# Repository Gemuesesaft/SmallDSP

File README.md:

# SmallDSP
a small, modular and affordable Audio DSP Module

The goal of this Project is to create a line-up of small DSP modules, centred
around an Analog Devices ADAU1463/67.
This Chip is easy to program with Sigma Studio, a node based development 
environment and pretty powerful for its price.

Current status:
- Dual: Rev 1.1: Layout finished, functionality has to be validated.
- Maxi: Rev 1.0: Layout finished, ,prototype ordered, 
    functionality has to be validated.
- Multi: Rev 1.0: Schematic unfinished.
- Mini: Nothing done yet.
- Micro: Nothing done yet.
- Digi: Nothing done yet.

I've planed for 6 different modules:

- A compact one with two analogue input and output channels (SmallDSP Dual).
- A very small with only digital I2S IOs (SmallDSP Digi).
- A very small module with only one analogue input and output (SmallDSPMini).
- A similar than the Mini, but with and Microphone preamp (SmallDSP Micro). 
    Perhaps powered by phantom power.
- One with 16 analogue IOs (SmallDSP Multi).
- And one with 32 analogue IOs (SmallDSP Maxi).

There are three different versions of the used DSP Chip:
- The ADAU1463WBCPZ150. This is a slower version (max. 150MHz) with 48kWords 
    data memory and 16kWords program memory. Optimal for the smaller Boards
    like the Dual, Mini or Micro.
- The ADAU1463WBCPZ300. This is a faster version (max. 300MHz) with the same
    48kWords data memory and 16kWords program memory. Well suited for heavy
    processing or many channels, for example the Multi or Maxi.
- And the ADAU1467WBCPZ300. This is also a faster version (max. 300MHz) with
    more memory 80kWords data and 24kWords program memory. The expanded memory
    is useful if long delays on multiple channels are required.
All versions are pin-compatible, so one can use the version, best suited for 
the use case. 

The Dual, Digi, Mini and if phantom power isn't possible, the Micro, shall be
powered by a single output wall brick power supply. Both Multi and Maxi are 
using a +-5V power supply and feature a PE connection. They are therefore
designed for a metal enclosure such a 19" Rack enclosure. 

I try to maximize the components covered by JLCPCBs Basic Parts library, so
the boards can be manufactured cheaply and easily. Unfortunately this doesn't
cover all components, so there is still some hand soldering necessary. 

I tried to avoid the use of a Microcontroller, because the DSP can do pretty
much everything on itself. Although the DSP can act as a I2C or SPI master, I 
used ADCs and DAC that are configured directly by setting specific pins,
because the usage of the I2C/SPI master feature an ADAU DSPs is, at least
to my knowledge, not very user-friendly. Please correct me if I'm wrong there 
I would very much like to know an easy way to use this feature.
The Maxi is an exception in that, as it has a STM32 MCU on board. That is 
because the used Codecs are only controllable over I2C/SPI and are way cheaper
than pin-controllable alternatives.

A detailed documentation is planned, but the current focus lies on finishing
the PCBs and the testing of those. Detailed performance measurements will
be published here as well, as soon as they are made.

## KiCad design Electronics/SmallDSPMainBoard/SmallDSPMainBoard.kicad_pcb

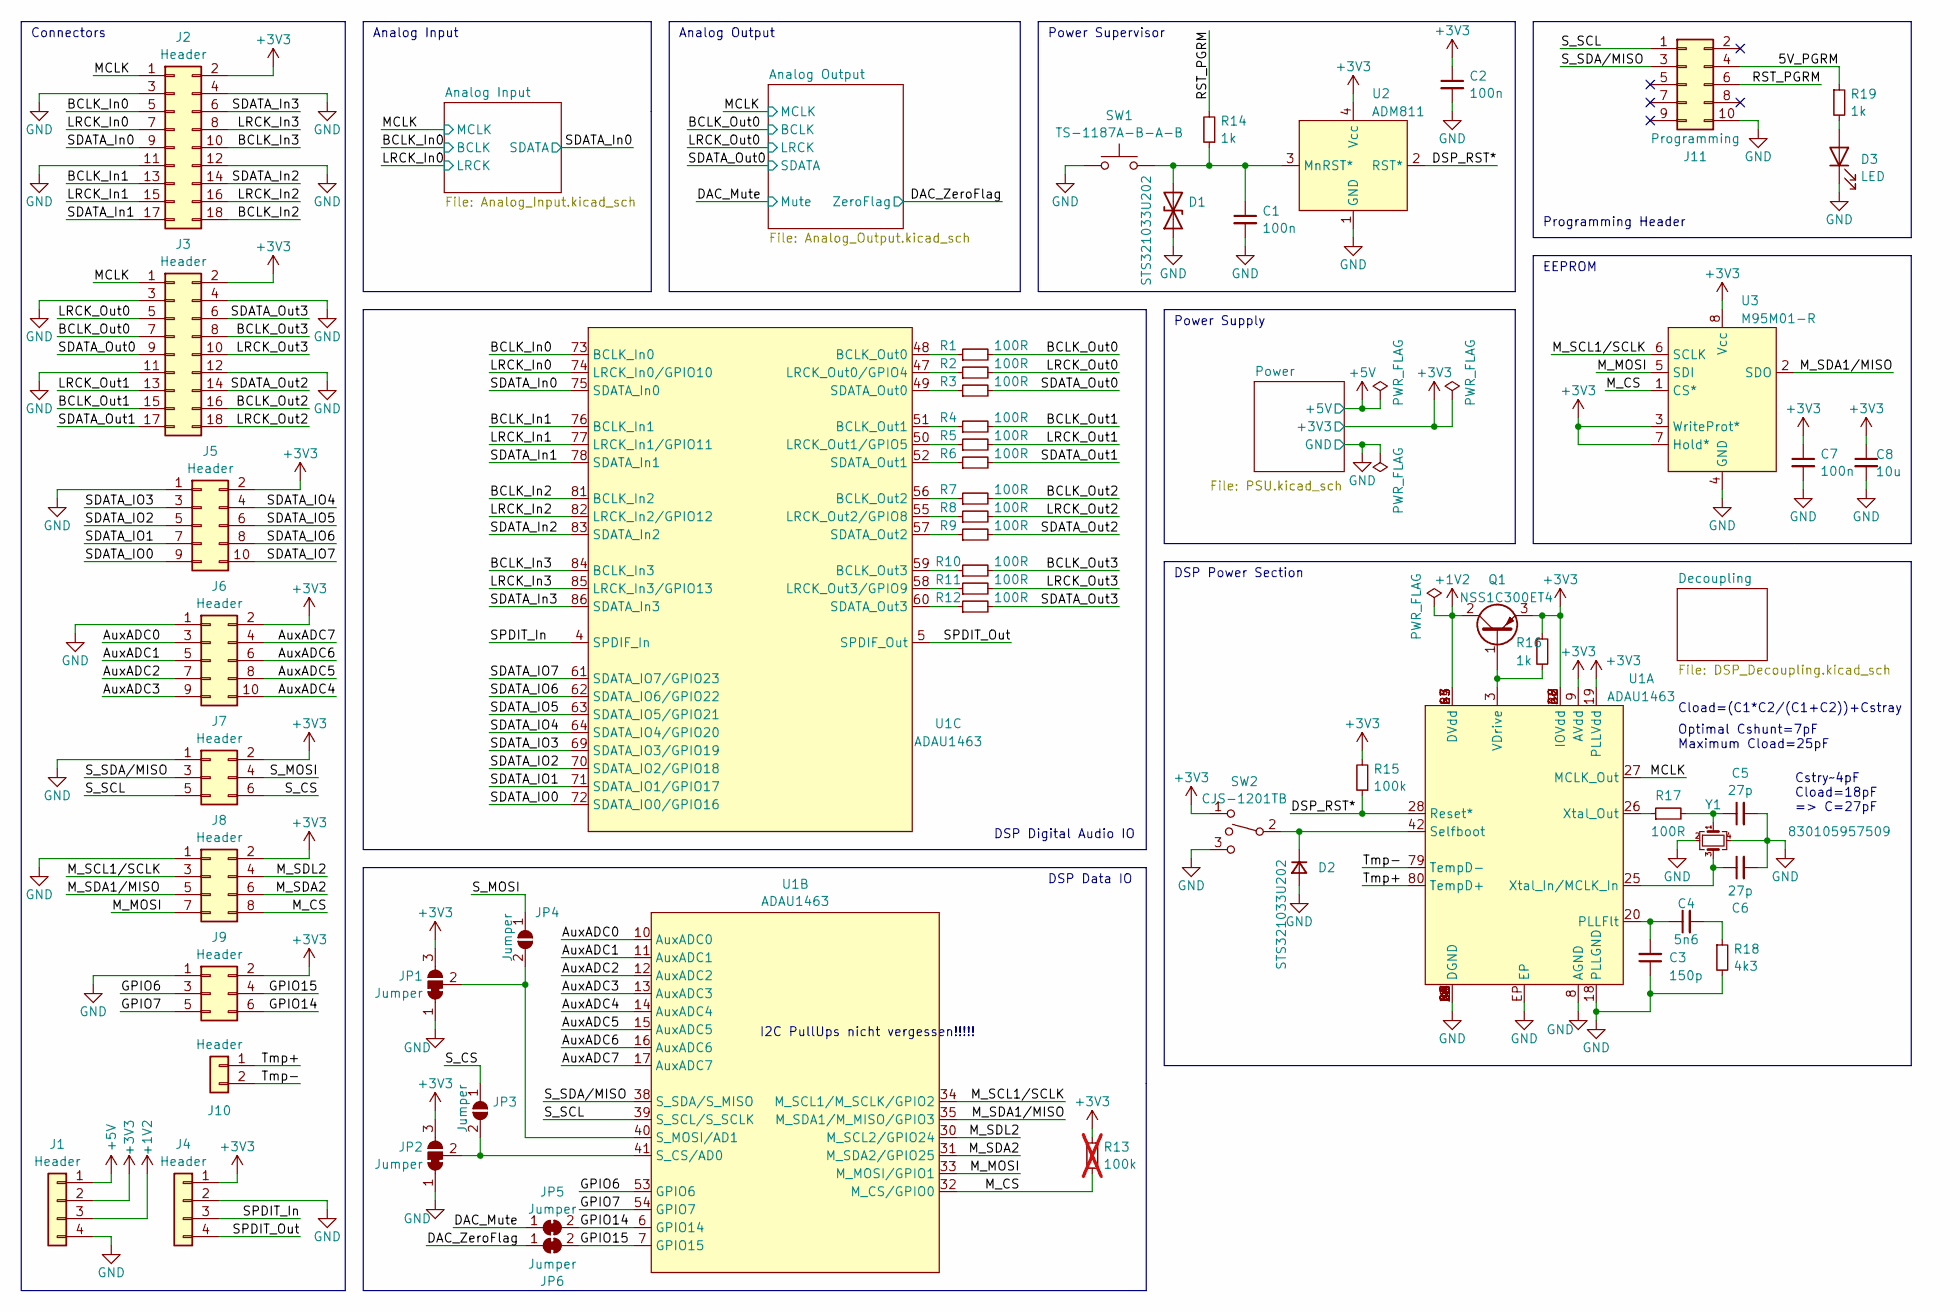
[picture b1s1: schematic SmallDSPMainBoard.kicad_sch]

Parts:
C1, C2, C7: 100n; C_0402_1005Metric; Rated Voltage 16V; Part Number CL05B104KO5NNNC; JLC Part Number C1525
C3: 150p; C_0402_1005Metric; Rated Voltage 50V; Part Number 0402B151K500NT; JLC Part Number C1527
C4: 5n6; C_0603_1608Metric_Pad1.08x0.95mm_HandSolder; Rated Voltage 50V; Part Number GRM1885C1H562JA01D
C5, C6: 27p; C_0402_1005Metric; Rated Voltage 50V; Part Number 0402CG270J500NT; JLC Part Number C1557
C8: 10u; C_0603_1608Metric; Rated Voltage 25V; Part Number CL10A106MA8NRNC; JLC Part Number C96446
D1, D2: STS321033U202; D_SOD-323_HandSoldering; Part Number STS321033U202
D3: LED; LED_0603_1608Metric; Part Number 19-217/BHC-ZL1M2RY/3T; JLC Part Number C72041
J1, J4: Header; PinHeader_1x04_P1.27mm_Vertical
J2, J3: Header; PinHeader_2x09_P1.27mm_Vertical
J5, J6: Header; PinHeader_2x05_P1.27mm_Vertical
J7, J9: Header; PinHeader_2x03_P1.27mm_Vertical
J8: Header; PinHeader_2x04_P1.27mm_Vertical
J10: Header; PinHeader_1x02_P1.27mm_Vertical
J11: Programming; IDC-Header_2x05_P2.54mm_Horizontal; Part Number 61201021721
JP1, JP2: Jumper; SolderJumper-3_P1.3mm_Bridged12_RoundedPad1.0x1.5mm
JP3, JP4: Jumper; SolderJumper-2_P1.3mm_Open_RoundedPad1.0x1.5mm
JP5, JP6: Jumper; SolderJumper-2_P1.3mm_Bridged_RoundedPad1.0x1.5mm
Q1: NSS1C300ET4; TO-252-2; Part Number NSS1C300ET4
R1, R2, R3, R4, R5, R6, R7, R8, R9, R10, R11, R12, R17: 100R; R_0402_1005Metric; Part Number 0402WGF1000TCE; JLC Part Number C25076
R13: 100k; R_0402_1005Metric; Part Number 0402WGF1003TCE; JLC Part Number C25741; not fitted
R14, R16, R19: 1k; R_0402_1005Metric; Part Number 0402WGF1001TCE; JLC Part Number C11702
R15: 100k; R_0402_1005Metric; Part Number 0402WGF1003TCE; JLC Part Number C25741
R18: 4k3; R_0603_1608Metric_Pad0.98x0.95mm_HandSolder; Part Number CR0603-FX-4301ELF
SW1: TS-1187A-B-A-B; Part Number TS-1187A-B-A-B; JLC Part Number C318884
SW2: CJS-1201TB; Part Number CJS-1201TB
U1: ADAU1463; Part Number ADAU1463
U2: ADM811; SOT-143_Handsoldering; Part Number ADM811TARTZ
U3: M95M01-R; SOIC-8_3.9x4.9mm_P1.27mm; Part Number M95M01-RMN
Y1: 830105957509; Crystal_SMD_3225-4Pin_3.2x2.5mm_HandSoldering; Part Number 830105957509

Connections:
+1V2: J1.3, Q1.2 (C), U1.24 (DVdd), U1.43 (DVdd), U1.65 (DVdd), U1.87 (DVdd); also elsewhere on the board
+3V3: C2.1, C7.1, C8.1, J1.2, J2.2, J3.2, J4.1, J5.2, J6.2, J7.2, J8.2, J9.2, JP1.3 (B), JP2.3 (B), Q1.3 (E), R13.2, R15.2, R16.1, SW2.1, U1.2 (IOVdd), U1.9 (AVdd), U1.19 (PLLVdd), U1.22 (IOVdd), U1.37 (IOVdd), U1.46 (IOVdd), U1.68 (IOVdd), U2.4 (Vcc), U3.3 (WriteProt*), U3.7 (Hold*), U3.8 (Vcc); also elsewhere on the board
+5V: J1.1; also elsewhere on the board
/5V_PGRM: J11.4, R19.1
/AuxADC0: J6.3, U1.10 (AuxADC0)
/AuxADC1: J6.5, U1.11 (AuxADC1)
/AuxADC2: J6.7, U1.12 (AuxADC2)
/AuxADC3: J6.9, U1.13 (AuxADC3)
/AuxADC4: J6.10, U1.14 (AuxADC4)
/AuxADC5: J6.8, U1.15 (AuxADC5)
/AuxADC6: J6.6, U1.16 (AuxADC6)
/AuxADC7: J6.4, U1.17 (AuxADC7)
/BCLK_In0: J2.5, U1.73 (BCLK_In0); also elsewhere on the board
/BCLK_In1: J2.13, U1.76 (BCLK_In1)
/BCLK_In2: J2.18, U1.81 (BCLK_In2)
/BCLK_In3: J2.10, U1.84 (BCLK_In3)
/BCLK_Out0: J3.7, R1.2; also elsewhere on the board
/BCLK_Out1: J3.15, R4.2
/BCLK_Out2: J3.16, R7.2
/BCLK_Out3: J3.8, R10.2
/DAC_Mute: JP5.1 (A); also elsewhere on the board
/DAC_ZeroFlag: JP6.1 (A); also elsewhere on the board
/DSP_RST*: R15.1, U1.28 (Reset*), U2.2 (RST*)
/GPIO6: J9.3, U1.53 (GPIO6)
/GPIO7: J9.5, U1.54 (GPIO7)
/GPIO14: J9.6, JP5.2 (B), U1.6 (GPIO14)
/GPIO15: J9.4, JP6.2 (B), U1.7 (GPIO15)
/LRCK_In0: J2.7, U1.74 (LRCK_In0/GPIO10); also elsewhere on the board
/LRCK_In1: J2.15, U1.77 (LRCK_In1/GPIO11)
/LRCK_In2: J2.16, U1.82 (LRCK_In2/GPIO12)
/LRCK_In3: J2.8, U1.85 (LRCK_In3/GPIO13)
/LRCK_Out0: J3.5, R2.2; also elsewhere on the board
/LRCK_Out1: J3.13, R5.2
/LRCK_Out2: J3.18, R8.2
/LRCK_Out3: J3.10, R11.2
/MCLK: J2.1, J3.1, U1.27 (MCLK_Out); also elsewhere on the board
/M_CS: J8.8, R13.1, U1.32 (M_CS/GPIO0), U3.1 (CS*)
/M_MOSI: J8.7, U1.33 (M_MOSI/GPIO1), U3.5 (SDI)
/M_SCL1/SCLK: J8.3, U1.34 (M_SCL1/M_SCLK/GPIO2), U3.6 (SCLK)
/M_SDA1/MISO: J8.5, U1.35 (M_SDA1/M_MISO/GPIO3), U3.2 (SDO)
/M_SDA2: J8.6, U1.31 (M_SDA2/GPIO25)
/M_SDL2: J8.4, U1.30 (M_SCL2/GPIO24)
/RST_PGRM: J11.6, R14.2
/SDATA_IO0: J5.9, U1.72 (SDATA_IO0/GPIO16)
/SDATA_IO1: J5.7, U1.71 (SDATA_IO1/GPIO17)
/SDATA_IO2: J5.5, U1.70 (SDATA_IO2/GPIO18)
/SDATA_IO3: J5.3, U1.69 (SDATA_IO3/GPIO19)
/SDATA_IO4: J5.4, U1.64 (SDATA_IO4/GPIO20)
/SDATA_IO5: J5.6, U1.63 (SDATA_IO5/GPIO21)
/SDATA_IO6: J5.8, U1.62 (SDATA_IO6/GPIO22)
/SDATA_IO7: J5.10, U1.61 (SDATA_IO7/GPIO23)
/SDATA_In0: J2.9, U1.75 (SDATA_In0); also elsewhere on the board
/SDATA_In1: J2.17, U1.78 (SDATA_In1)
/SDATA_In2: J2.14, U1.83 (SDATA_In2)
/SDATA_In3: J2.6, U1.86 (SDATA_In3)
/SDATA_Out0: J3.9, R3.2; also elsewhere on the board
/SDATA_Out1: J3.17, R6.2
/SDATA_Out2: J3.14, R9.2
/SDATA_Out3: J3.6, R12.2
/SPDIT_In: J4.3, U1.4 (SPDIF_In)
/SPDIT_Out: J4.4, U1.5 (SPDIF_Out)
/S_CS: J7.6, JP3.1 (A)
/S_MOSI: J7.4, JP4.1 (A)
/S_SCL: J7.5, J11.1, U1.39 (S_SCL/S_SCLK)
/S_SDA/MISO: J7.3, J11.3, U1.38 (S_SDA/S_MISO)
/Tmp+: J10.1, U1.80 (TempD+)
/Tmp-: J10.2, U1.79 (TempD-)
GND: C1.2, C2.2, C3.1, C5.2, C6.2, C7.2, C8.2, D1.1 (A1), D2.2 (A), D3.1 (K), J1.4, J2.3, J2.4, J2.11, J2.12, J3.3, J3.4, J3.11, J3.12, J4.2, J5.1, J6.1, J7.1, J8.1, J9.1, J11.10, JP1.1 (A), JP2.1 (A), R18.2, SW1.1, SW2.3, U1.1 (DGND), U1.8 (AGND), U1.18 (PLLGND), U1.21 (DGND), U1.23 (DGND), U1.29 (DGND), U1.36 (DGND), U1.44 (DGND), U1.45 (DGND), U1.66 (DGND), U1.67 (DGND), U1.88 (DGND), U1.EP, U2.1 (GND), U3.4 (GND), Y1.2, Y1.4; also elsewhere on the board
unnamed: C4.2, R18.1
unnamed: C5.1, R17.2, Y1.1
unnamed: C1.1, D1.2 (A2), R14.1, SW1.2, U2.3 (MnRST*)
unnamed: D2.1 (K), SW2.2, U1.42 (Selfboot)
unnamed: D3.2 (A), R19.2
unnamed: JP1.2 (C), JP4.2 (B), U1.40 (S_MOSI/AD1)
unnamed: JP2.2 (C), JP3.2 (B), U1.41 (S_CS/AD0)
unnamed: Q1.1 (B), R16.2, U1.3 (VDrive)
unnamed: C3.2, C4.1, U1.20 (PLLFlt)
unnamed: C6.1, U1.25 (Xtal_In/MCLK_In), Y1.3
unnamed: R17.1, U1.26 (Xtal_Out)
unnamed: R1.1, U1.48 (BCLK_Out0)
unnamed: R4.1, U1.51 (BCLK_Out1)
unnamed: R7.1, U1.56 (BCLK_Out2)
unnamed: R10.1, U1.59 (BCLK_Out3)
unnamed: R2.1, U1.47 (LRCK_Out0/GPIO4)
unnamed: R5.1, U1.50 (LRCK_Out1/GPIO5)
unnamed: R8.1, U1.55 (LRCK_Out2/GPIO8)
unnamed: R11.1, U1.58 (LRCK_Out3/GPIO9)
unnamed: R3.1, U1.49 (SDATA_Out0)
unnamed: R6.1, U1.52 (SDATA_Out1)
unnamed: R9.1, U1.57 (SDATA_Out2)
unnamed: R12.1, U1.60 (SDATA_Out3)

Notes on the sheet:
DSP Data IO
EEPROM
DSP Digital Audio IO
Power Supervisor
Power Supply
I2C PullUps nicht vergessen!!!!!
Cload=(C1*C2/(C1+C2))+Cstray
Analog Output
Connectors
Programming Header
Optimal Cshunt=7pF Maximum Cload=25pF
DSP Power Section
Cstry~4pF Cload=18pF => C=27pF
Analog Input

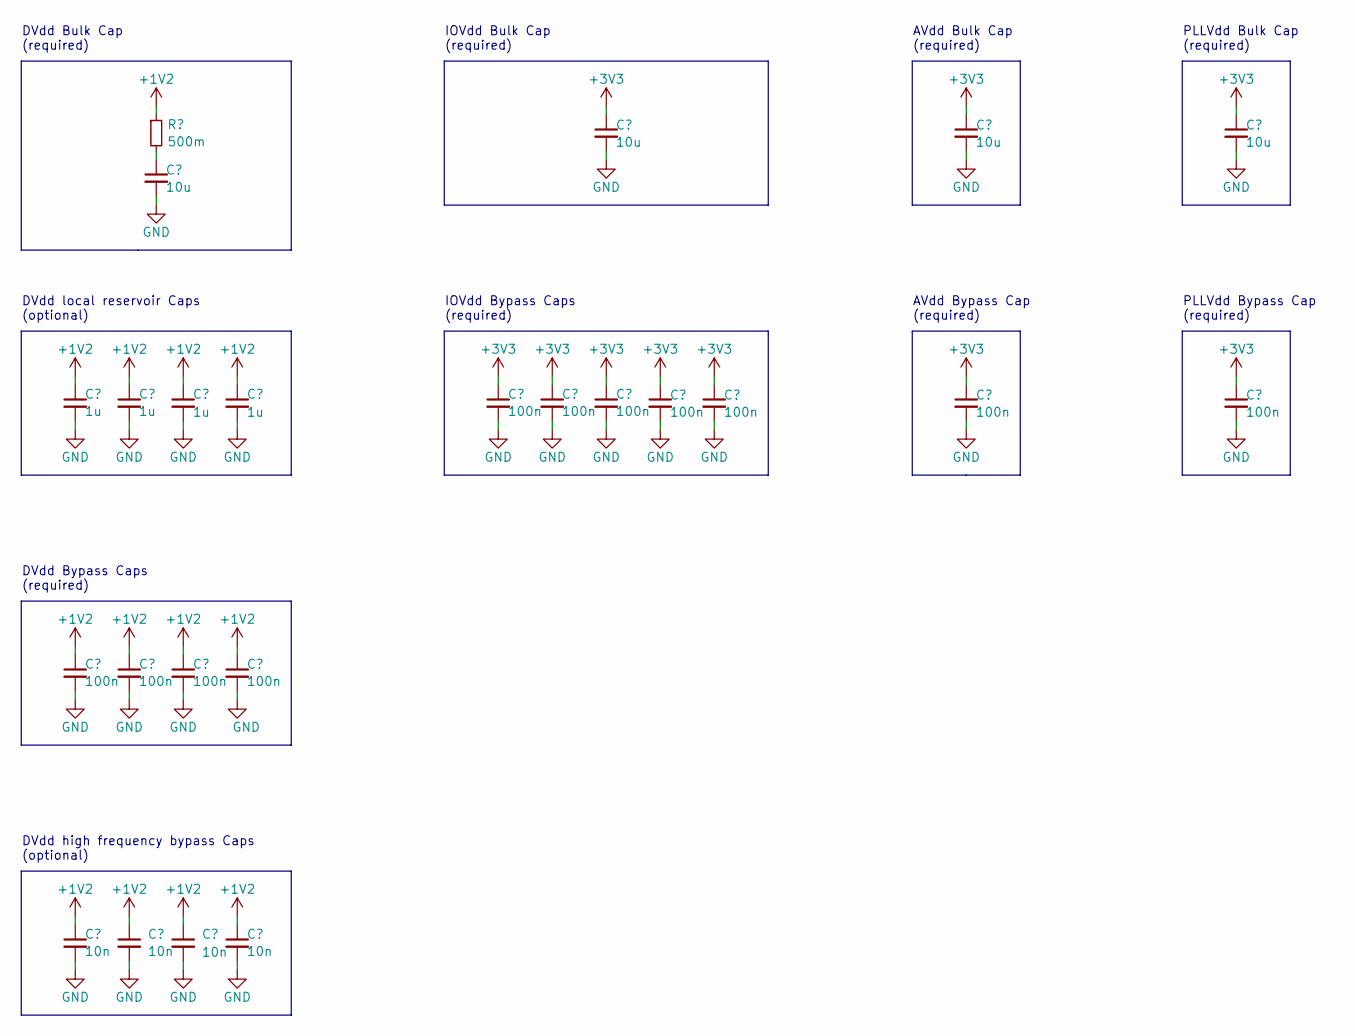
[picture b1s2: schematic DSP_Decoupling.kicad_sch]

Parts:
C60, C63, C67, C70: 1u; C_0402_1005Metric; Rated Voltage 25V; Part Number CL05A105KA5NQNC; JLC Part Number C52923
C61, C64, C68, C71, C73, C74, C76, C77, C78, C80, C82: 100n; C_0402_1005Metric; Rated Voltage 16V; Part Number CL05B104KO5NNNC; JLC Part Number C1525
C62, C65, C69, C72: 10n; C_0402_1005Metric; Rated Voltage 50V; Part Number CL05B103KB5NNNC; JLC Part Number C15195
C66, C75, C79, C81: 10u; C_0603_1608Metric; Rated Voltage 25V; Part Number CL10A106MA8NRNC; JLC Part Number C96446
R64: 500m; R_0603_1608Metric_Pad0.98x0.95mm_HandSolder; Part Number MFL0603R5000FB

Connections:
+1V2: C60.1, C61.1, C62.1, C63.1, C64.1, C65.1, C67.1, C68.1, C69.1, C70.1, C71.1, C72.1, R64.1; also elsewhere on the board
+3V3: C73.1, C74.1, C75.1, C76.1, C77.1, C78.1, C79.1, C80.1, C81.1, C82.1; also elsewhere on the board
GND: C60.2, C61.2, C62.2, C63.2, C64.2, C65.2, C66.2, C67.2, C68.2, C69.2, C70.2, C71.2, C72.2, C73.2, C74.2, C75.2, C76.2, C77.2, C78.2, C79.2, C80.2, C81.2, C82.2; also elsewhere on the board
unnamed: C66.1, R64.2

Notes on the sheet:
IOVdd Bypass Caps (required)
DVdd Bulk Cap (required)
PLLVdd Bypass Cap (required)
DVdd local reservoir Caps (optional)
IOVdd Bulk Cap (required)
DVdd Bypass Caps (required)
AVdd Bulk Cap (required)
AVdd Bypass Cap (required)
PLLVdd Bulk Cap (required)
DVdd high frequency bypass Caps (optional)

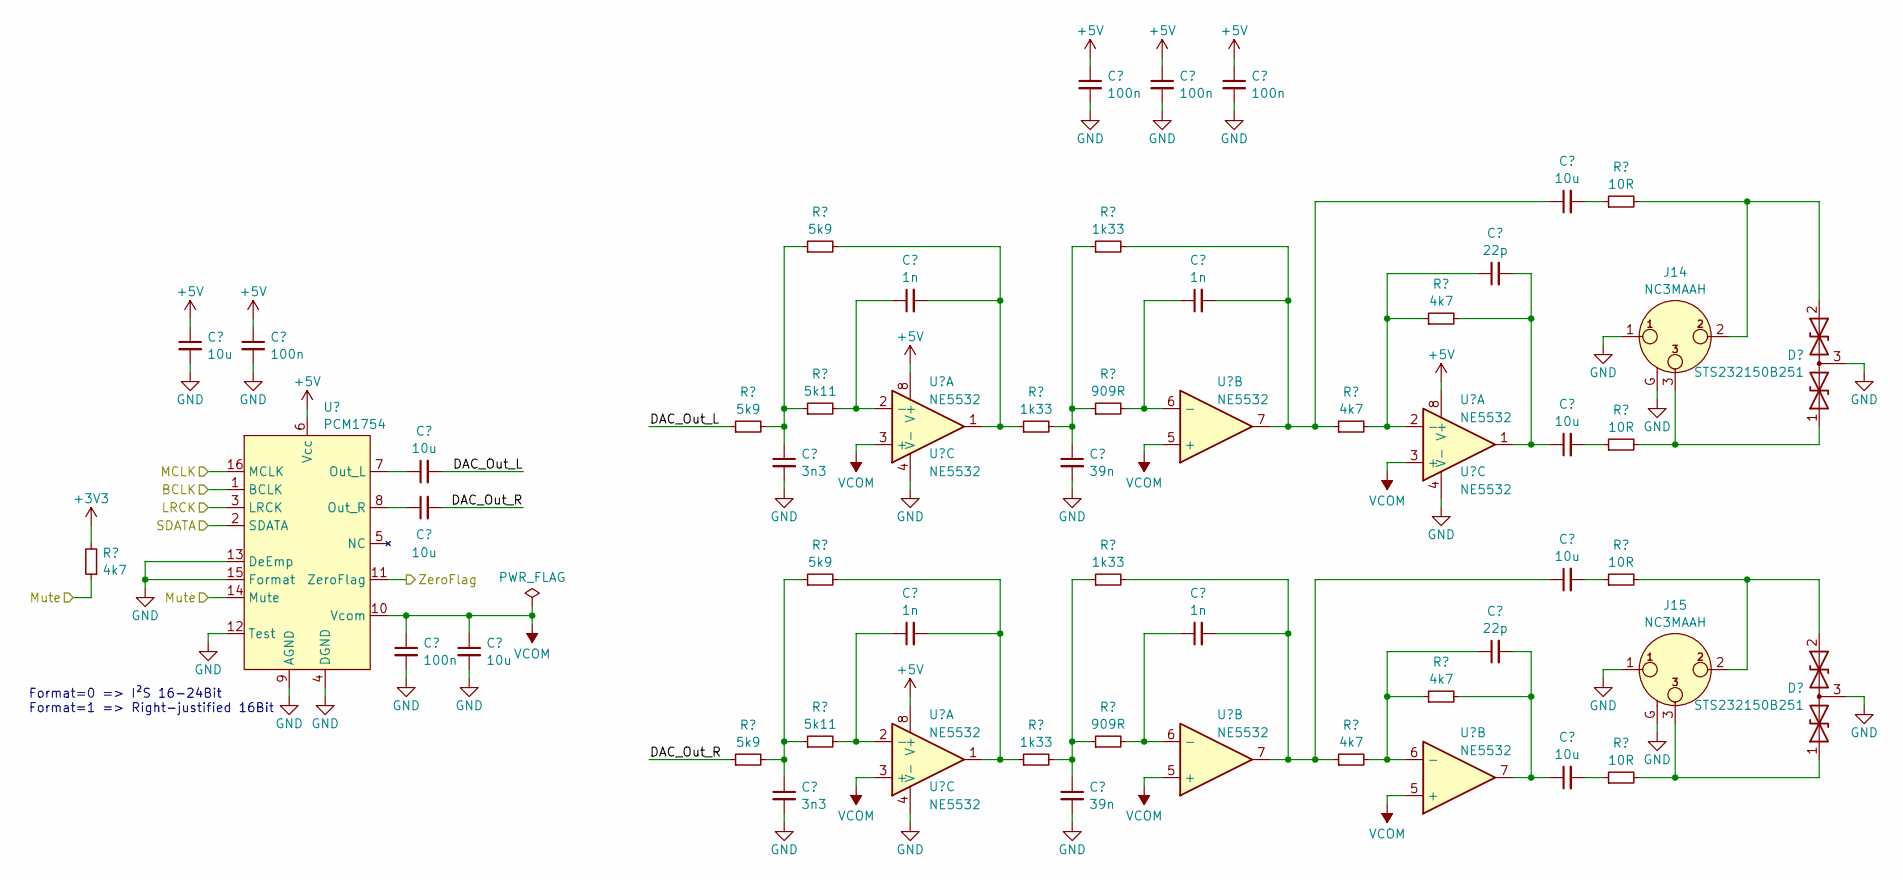
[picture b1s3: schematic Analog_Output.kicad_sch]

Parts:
C30, C35: 10u; C_0603_1608Metric; Rated Voltage 25V; Part Number CL10A106MA8NRNC; JLC Part Number C96446
C31, C32, C42, C43, C46: 100n; C_0402_1005Metric; Rated Voltage 16V; Part Number CL05B104KO5NNNC; JLC Part Number C1525
C33, C34, C49, C50, C51, C52: 10u; C_1206_3216Metric; Rated Voltage 50V; Part Number CL31A106KBHNNNE; JLC Part Number C13585
C36, C37: 3n3; C_0603_1608Metric_Pad1.08x0.95mm_HandSolder; Rated Voltage 50V; Part Number GRM1885C1H332JA01J
C38, C39, C44, C45: 1n; C_0603_1608Metric_Pad1.08x0.95mm_HandSolder; Rated Voltage 50V; Part Number GRM1885C1H102JA01D
C40, C41: 39n; C_0805_2012Metric_Pad1.18x1.45mm_HandSolder; Rated Voltage 100V; Part Number GRM2195C2A393JE01D
C47, C48: 22p; C_0402_1005Metric; Rated Voltage 50V; Part Number 0402CG220J500NT; JLC Part Number C1555
D8, D9: STS232150B251; SOT-23-3; Part Number STS232150B251
J14, J15: NC3MAAH; Jack_XLR_Neutrik_NC3MAAH_Horizontal; Part Number NC3MAAH
R43, R56, R57, R58, R59: 4k7; R_0402_1005Metric; Part Number 0402WGF4701TCE; JLC Part Number C25900
R44, R45, R46, R48: 5k9; R_0603_1608Metric_Pad0.98x0.95mm_HandSolder; Part Number CR0603-FX-5901ELF
R47, R49: 5k11; R_0603_1608Metric_Pad0.98x0.95mm_HandSolder; Part Number CR0603-FX-5111ELF
R50, R51, R52, R54: 1k33; R_0603_1608Metric_Pad0.98x0.95mm_HandSolder; Part Number CR0603-FX-1331ELF
R53, R55: 909R; R_0603_1608Metric_Pad0.98x0.95mm_HandSolder; Part Number CR0603-FX-9090ELF
R60, R61, R62, R63: 10R; R_0402_1005Metric; Part Number 0402WGF100JTCE; JLC Part Number C25077
U8: PCM1754; SSOP-16_3.9x4.9mm_P0.635mm; Part Number PCM1754
U9, U10, U11: NE5532; SOIC-8_3.9x4.9mm_P1.27mm; Part Number NE5532DR; JLC Part Number C7426

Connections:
+3V3: R43.2; also elsewhere on the board
+5V: C30.1, C31.1, C42.1, C43.1, C46.1, U8.6 (Vcc), U9.8 (V+), U10.8 (V+), U11.8 (V+); also elsewhere on the board
/Analog Output/DAC_Out_L: C33.2, R44.1
/Analog Output/DAC_Out_R: C34.2, R45.1
/BCLK_Out0: U8.1 (BCLK); also elsewhere on the board
/DAC_Mute: R43.1, U8.14 (Mute); also elsewhere on the board
/DAC_ZeroFlag: U8.11 (ZeroFlag); also elsewhere on the board
/LRCK_Out0: U8.3 (LRCK); also elsewhere on the board
/MCLK: U8.16 (MCLK); also elsewhere on the board
/SDATA_Out0: U8.2 (SDATA); also elsewhere on the board
GND: C30.2, C31.2, C32.2, C35.2, C36.2, C37.2, C40.2, C41.2, C42.2, C43.2, C46.2, D8.3 (common), D9.3 (common), J14.1, J14.G, J15.1, J15.G, U8.4 (DGND), U8.9 (AGND), U8.12 (Test), U8.13 (DeEmp), U8.15 (Format), U9.4 (V-), U10.4 (V-), U11.4 (V-); also elsewhere on the board
unnamed: C36.1, R44.2, R46.1, R47.1
unnamed: C37.1, R45.2, R48.1, R49.1
unnamed: C38.2, R46.2, R50.1, U9.1
unnamed: C39.2, R48.2, R51.1, U10.1
unnamed: C40.1, R50.2, R52.1, R53.1
unnamed: C41.1, R51.2, R54.1, R55.1
unnamed: C44.2, C49.1, R52.2, R56.1, U9.7
unnamed: C45.2, C51.1, R54.2, R57.1, U10.7
unnamed: C47.2, C50.1, R58.2, U11.1
unnamed: C48.2, C52.1, R59.2, U11.7
unnamed: C49.2, R60.1
unnamed: C50.2, R61.1
unnamed: C51.2, R62.1
unnamed: C52.2, R63.1
unnamed: D8.1 (A1), J14.3, R61.2
unnamed: D8.2 (A2), J14.2, R60.2
unnamed: D9.1 (A1), J15.3, R63.2
unnamed: D9.2 (A2), J15.2, R62.2
unnamed: C33.1, U8.7 (Out_L)
unnamed: C34.1, U8.8 (Out_R)
unnamed: C38.1, R47.2, U9.2 (-)
unnamed: C44.1, R53.2, U9.6 (-)
unnamed: C39.1, R49.2, U10.2 (-)
unnamed: C45.1, R55.2, U10.6 (-)
unnamed: C47.1, R56.2, R58.1, U11.2 (-)
unnamed: C48.1, R57.2, R59.1, U11.6 (-)
VCOM: C32.1, C35.1, U8.10 (Vcom), U9.3 (+), U9.5 (+), U10.3 (+), U10.5 (+), U11.3 (+), U11.5 (+); also elsewhere on the board

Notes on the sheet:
Format=0 => I²S 16-24Bit Format=1 => Right-justified 16Bit

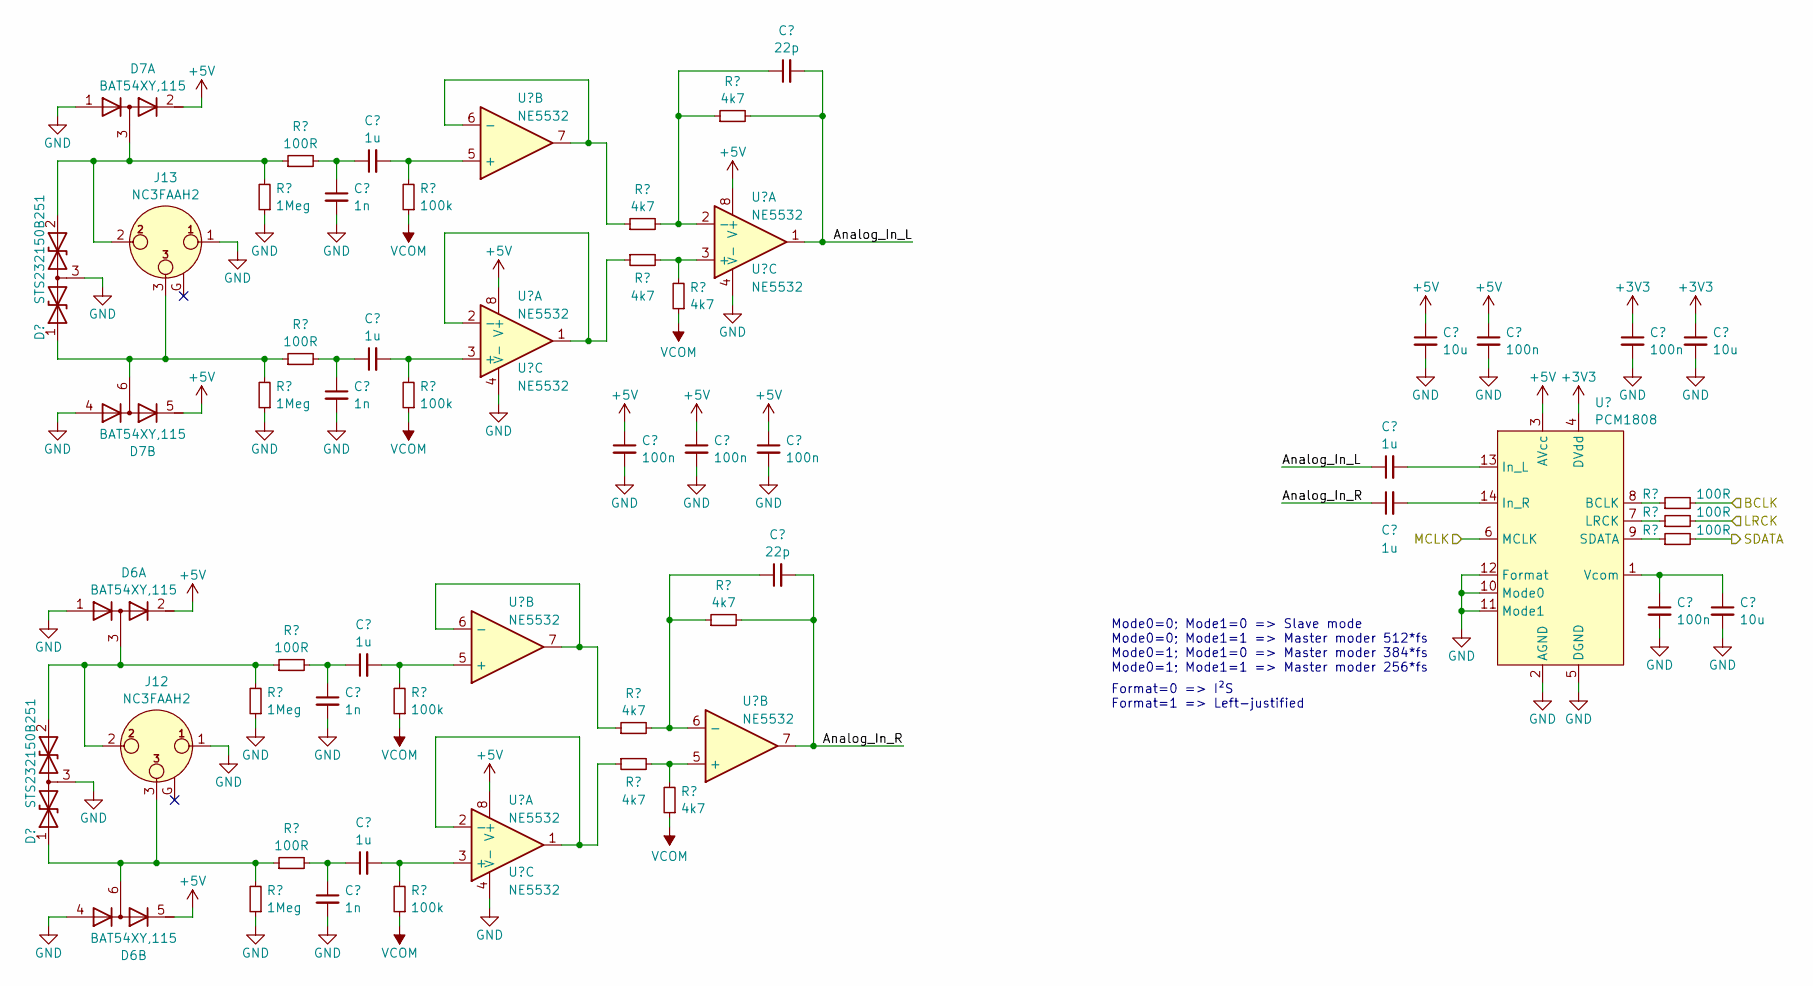
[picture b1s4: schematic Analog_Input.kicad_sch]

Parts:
C9, C10, C11, C12: 1n; C_0603_1608Metric_Pad1.08x0.95mm_HandSolder; Rated Voltage 50V; Part Number GRM1885C1H102JA01D
C13, C14, C15, C16, C22, C23: 1u; C_1206_3216Metric; Rated Voltage 50V; Part Number CL31B105KBHNNNE; JLC Part Number C1848
C17, C18, C19, C25, C26, C27: 100n; C_0402_1005Metric; Rated Voltage 16V; Part Number CL05B104KO5NNNC; JLC Part Number C1525
C20, C21: 22p; C_0402_1005Metric; Rated Voltage 50V; Part Number 0402CG220J500NT; JLC Part Number C1555
C24, C28, C29: 10u; C_0603_1608Metric; Rated Voltage 25V; Part Number CL10A106MA8NRNC; JLC Part Number C96446
D4, D5: STS232150B251; SOT-23-3; Part Number STS232150B251
D6, D7: BAT54XY,115; SOT-363_SC-70-6_Handsoldering; Part Number BAT54XY,115
J12, J13: NC3FAAH2; Jack_XLR_Neutrik_NC3FAAH2_Horizontal; Part Number NC3FAAH2
R20, R21, R22, R23: 1Meg; R_0402_1005Metric; Part Number 0402WGF1004TCE; JLC Part Number C26083
R24, R25, R26, R27, R40, R41, R42: 100R; R_0402_1005Metric; Part Number 0402WGF1000TCE; JLC Part Number C25076
R28, R29, R30, R31: 100k; R_0402_1005Metric; Part Number 0402WGF1003TCE; JLC Part Number C25741
R32, R33, R34, R35, R36, R37, R38, R39: 4k7; R_0402_1005Metric; Part Number 0402WGF4701TCE; JLC Part Number C25900
U4, U5, U6: NE5532; SOIC-8_3.9x4.9mm_P1.27mm; Part Number NE5532DR; JLC Part Number C7426
U7: PCM1808; TSSOP-14_4.4x5mm_P0.65mm; Part Number PCM1808

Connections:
+3V3: C26.1, C28.1, U7.4 (DVdd); also elsewhere on the board
+5V: C17.1, C18.1, C19.1, C24.1, C25.1, D6.2 (K1), D6.5 (K2), D7.2 (K1), D7.5 (K2), U4.8 (V+), U5.8 (V+), U6.8 (V+), U7.3 (AVcc); also elsewhere on the board
/Analog Input/Analog_In_L: C21.2, C22.1, R39.2, U6.1
/Analog Input/Analog_In_R: C20.2, C23.1, R38.2, U6.7
/BCLK_In0: R40.2; also elsewhere on the board
/LRCK_In0: R41.2; also elsewhere on the board
/MCLK: U7.6 (MCLK); also elsewhere on the board
/SDATA_In0: R42.2; also elsewhere on the board
GND: C9.2, C10.2, C11.2, C12.2, C17.2, C18.2, C19.2, C24.2, C25.2, C26.2, C27.2, C28.2, C29.2, D4.3 (common), D5.3 (common), D6.1 (A1), D6.4 (A2), D7.1 (A1), D7.4 (A2), J12.1, J13.1, R20.1, R21.1, R22.1, R23.1, U4.4 (V-), U5.4 (V-), U6.4 (V-), U7.2 (AGND), U7.5 (DGND), U7.10 (Mode0), U7.11 (Mode1), U7.12 (Format); also elsewhere on the board
unnamed: C10.1, C14.1, R25.2
unnamed: C11.1, C15.1, R26.2
unnamed: C12.1, C16.1, R27.2
unnamed: C9.1, C13.1, R24.2
unnamed: D4.1 (A1), D6.6 (C2), J12.3, R21.2, R25.1
unnamed: D4.2 (A2), D6.3 (C1), J12.2, R20.2, R24.1
unnamed: D5.1 (A1), D7.6 (C2), J13.3, R23.2, R27.1
unnamed: D5.2 (A2), D7.3 (C1), J13.2, R22.2, R26.1
unnamed: C14.2, R29.2, U4.3 (+)
unnamed: R33.1, U4.1, U4.2 (-)
unnamed: C13.2, R28.2, U4.5 (+)
unnamed: R32.1, U4.6 (-), U4.7
unnamed: C16.2, R31.2, U5.3 (+)
unnamed: R35.1, U5.1, U5.2 (-)
unnamed: C15.2, R30.2, U5.5 (+)
unnamed: R34.1, U5.6 (-), U5.7
unnamed: R35.2, R37.2, U6.3 (+)
unnamed: C21.1, R34.2, R39.1, U6.2 (-)
unnamed: R33.2, R36.2, U6.5 (+)
unnamed: C20.1, R32.2, R38.1, U6.6 (-)
unnamed: R40.1, U7.8 (BCLK)
unnamed: C22.2, U7.13 (In_L)
unnamed: C23.2, U7.14 (In_R)
unnamed: R41.1, U7.7 (LRCK)
unnamed: R42.1, U7.9 (SDATA)
unnamed: C27.1, C29.1, U7.1 (Vcom)
VCOM: R28.1, R29.1, R30.1, R31.1, R36.1, R37.1; also elsewhere on the board

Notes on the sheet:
Mode0=0; Mode1=0 => Slave mode Mode0=0; Mode1=1 => Master moder 512*fs Mode0=1; Mode1=0 => Master moder 384*fs Mode0=1; Mode1=1 => Master moder 256*fs
Format=0 => I²S Format=1 => Left-justified

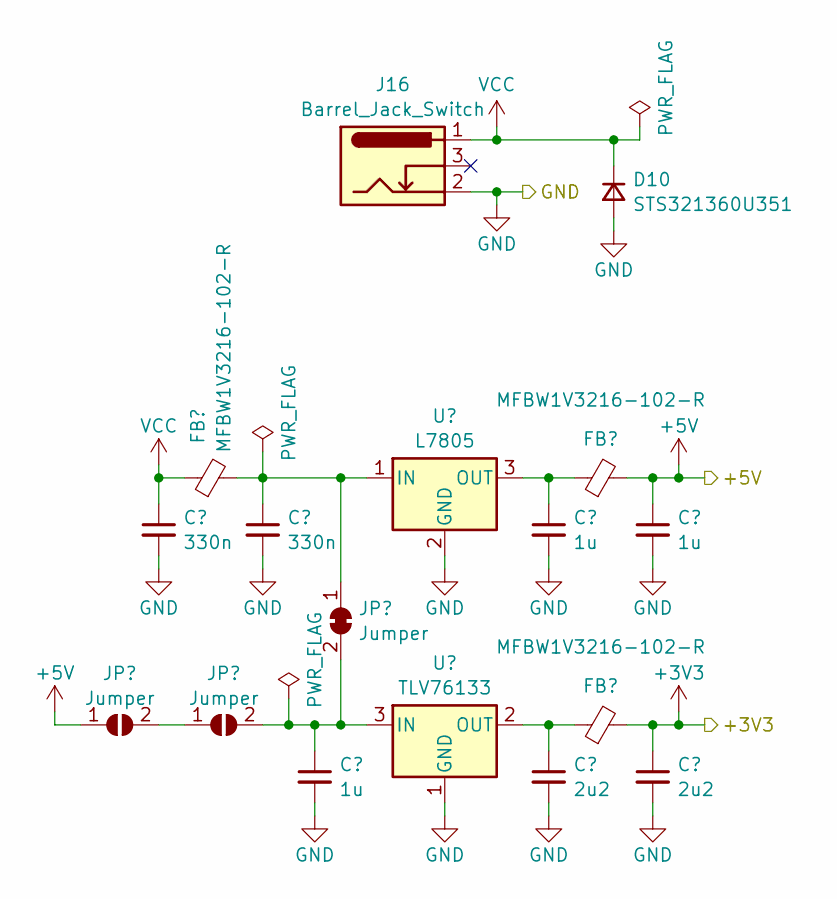
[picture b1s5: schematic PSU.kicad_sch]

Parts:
C53, C54: 330n; C_0805_2012Metric; Rated Voltage 50V; Part Number 0805B334K500NT; JLC Part Number C1740
C55, C56, C58: 1u; C_0805_2012Metric; Rated Voltage 50V; Part Number CL21B105KBFNNNE; JLC Part Number C28323
C57, C59: 2u2; C_0603_1608Metric; Rated Voltage 16V; Part Number CL10A225KO8NNNC; JLC Part Number C23630
D10: STS321360U351; D_SOD-323_HandSoldering; Part Number STS321360U351
FB1, FB2, FB3: MFBW1V3216-102-R; R_0603_1608Metric_Pad0.98x0.95mm_HandSolder; Part Number BBPY00201209601Y00
J16: Barrel_Jack_Switch; BarrelJack_CUI_PJ-079BH_Horizontal; Part Number PJ-079BH
JP7, JP8: Jumper; SolderJumper-2_P1.3mm_Open_RoundedPad1.0x1.5mm
JP9: Jumper; SolderJumper-2_P1.3mm_Bridged_RoundedPad1.0x1.5mm
U12: L7805; TO-252-2; Part Number MC7805BDTG
U13: TLV76133; SOT-223-3_TabPin2; Part Number TLV76133

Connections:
+3V3: C59.1, FB3.2; also elsewhere on the board
+5V: C58.1, FB2.2, JP7.1 (A); also elsewhere on the board
GND: C53.2, C54.2, C55.2, C56.2, C57.2, C58.2, C59.2, D10.2 (A), J16.2, U12.2 (GND), U13.1 (GND); also elsewhere on the board
unnamed: JP7.2 (B), JP8.1 (A)
unnamed: C55.1, JP8.2 (B), JP9.2 (B), U13.3 (IN)
unnamed: C54.1, FB1.2, JP9.1 (A), U12.1 (IN)
unnamed: C56.1, FB2.1, U12.3 (OUT)
unnamed: C57.1, FB3.1, U13.2 (OUT)
VCC: C53.1, D10.1 (K), FB1.1, J16.1

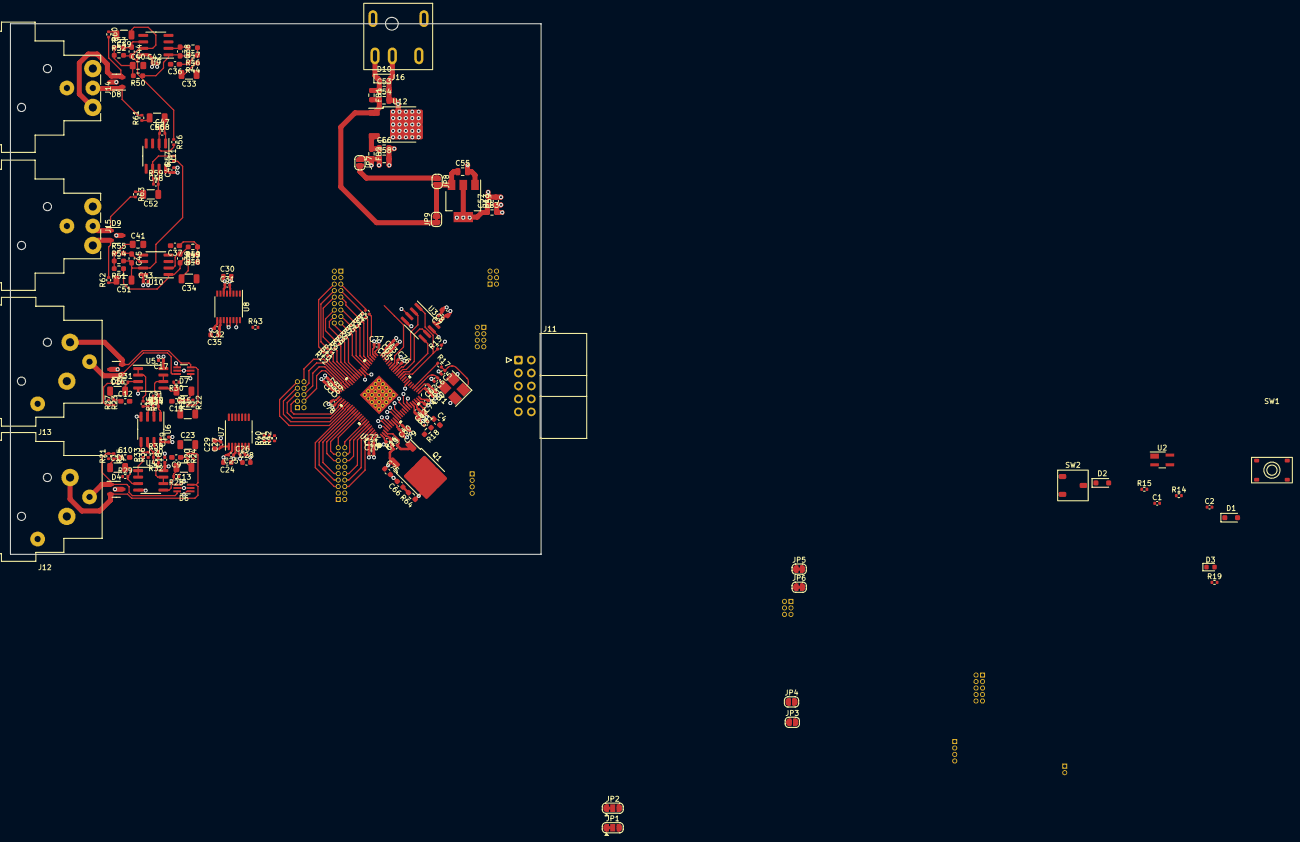
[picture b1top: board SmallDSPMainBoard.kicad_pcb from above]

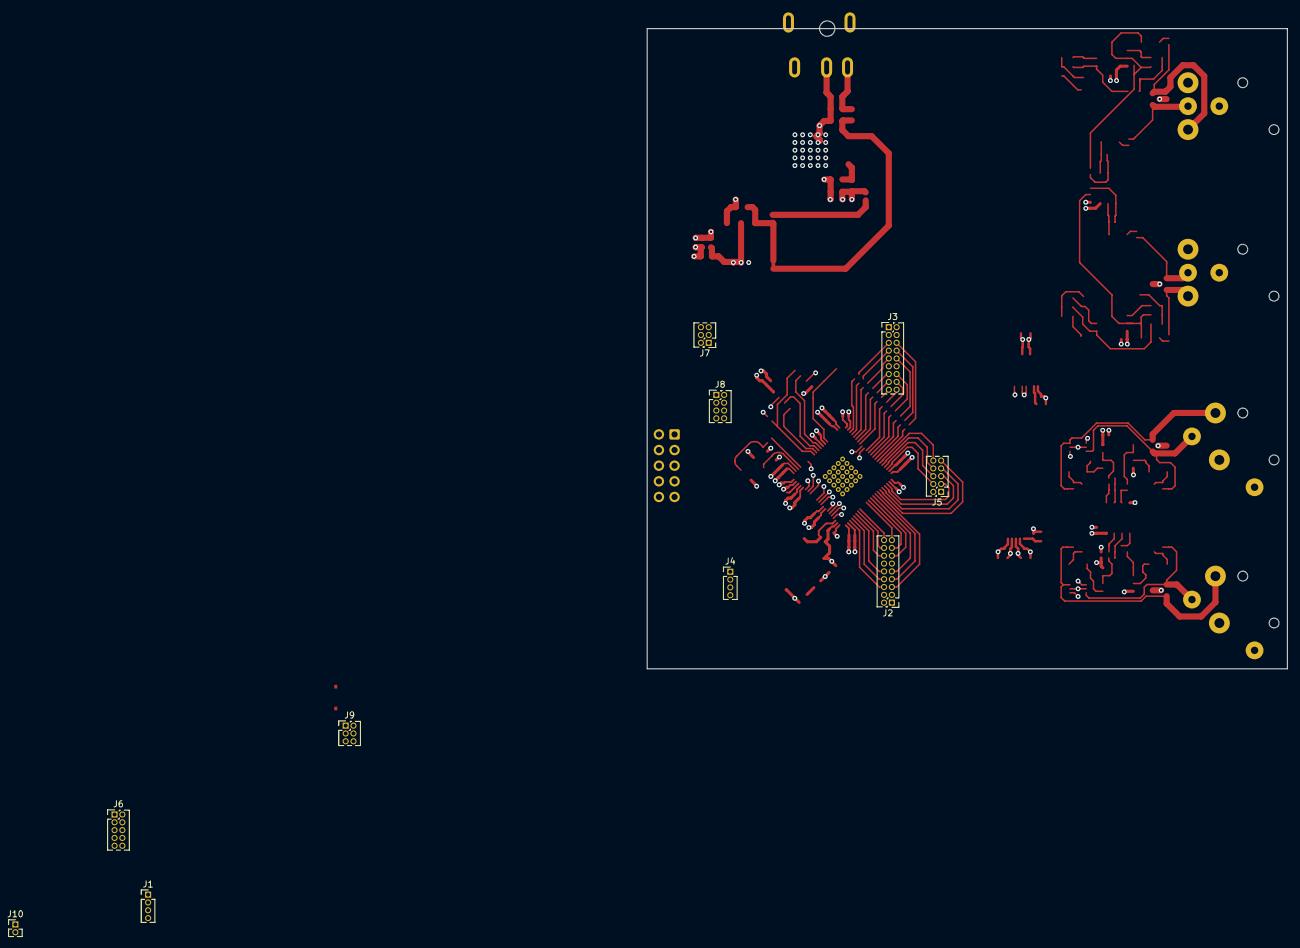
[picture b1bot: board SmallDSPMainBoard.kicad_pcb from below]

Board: 2 copper layers, 104.0 x 104.0 mm, 201 parts (10 on the bottom side), 155 nets.

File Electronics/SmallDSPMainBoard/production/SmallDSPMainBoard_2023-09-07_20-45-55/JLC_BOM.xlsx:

Designator | Footprint | Quantity | Value | LCSC Part #
C1, C17, C18, C19, C2, C25, C26, C27, C31, C32, C42, C43, C46, C60, C63, C67, C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 | 0402 | 25 | 100n | C1525
C10, C11, C12, C38, C39, C44, C45, C9 | 0603 | 8 | 1n
C13, C14, C15, C16, C22, C23 | 1206 | 6 | 1u
C20, C21, C47, C48 | 0402 | 4 | 22p
C24, C28, C29, C30, C35, C65, C74, C78, C8, C80 | 0603 | 10 | 10u
C3 | 0402 | 1 | 150p
C33, C34, C49, C50, C51, C52 | 1206 | 6 | 10u
C36, C37 | 0603 | 2 | 3n3
C4 | 0603 | 1 | 5n6
C40, C41 | 0805 | 2 | 39n
C5, C6 | 0402 | 2 | 27p
C53, C54, C55, C56, C57, C58 | 0805 | 6 | 1u
C59, C62, C66, C69 | 0402 | 4 | 1u
C61, C64, C68, C71 | 0402 | 4 | 10n
D1, D2 | D_SOD-323_HandSoldering | 2 | STS321033U202
D10, D12, D13, D14, D3 | 0603 | 5 | LED
D11 | D_SOD-323_HandSoldering | 1 | STS321360U351
D4, D5, D8, D9 | SOT-23-3 | 4 | STS232150B251
D6, D7 | SOT-363_SC-70-6_Handsoldering | 2 | BAT54XY,115
FB1, FB2, FB3 | 0603 | 3 | MFBW1V3216-102-R
H1, H2, H3, H4 | MountingHole_3.2mm_M3_ISO7380 | 4 | MountingHole
J1, J4 | PinHeader_1x04_P1.27mm_Vertical | 2 | Header
J10 | PinHeader_1x02_P1.27mm_Vertical | 1 | Header
J11 | IDC-Header_2x05_P2.54mm_Horizontal | 1 | Programming
J12, J13 | Jack_XLR_Neutrik_NC3FAAH2_Horizontal | 2 | NC3FAAH2
J14, J15 | Jack_XLR_Neutrik_NC3MAAH_Horizontal | 2 | NC3MAAH
J16 | BarrelJack_CUI_PJ-079BH_Horizontal | 1 | Barrel_Jack_Switch
J2, J3 | PinHeader_2x09_P1.27mm_Vertical | 2 | Header
J5, J6 | PinHeader_2x05_P1.27mm_Vertical | 2 | Header
J7, J9 | PinHeader_2x03_P1.27mm_Vertical | 2 | Header
J8 | PinHeader_2x04_P1.27mm_Vertical | 1 | Header
JP1, JP2 | SolderJumper-3_P1.3mm_Bridged12_RoundedPad1.0x1.5mm | 2 | Jumper
JP3, JP4 | SolderJumper-2_P1.3mm_Open_RoundedPad1.0x1.5mm | 2 | Jumper
JP5, JP6 | SolderJumper-2_P1.3mm_Bridged_RoundedPad1.0x1.5mm | 2 | Jumper
Q1 | TO-252-2 | 1 | NSS1C300ET4
Q2, Q3 | SOT-23 | 2 | MMBT3904
R1, R10, R11, R12, R17, R2, R24, R25, R26, R27, R3, R4, R40, R41, R42, R5, R6, 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 | 0402 | 21 | 100R
R13 | 0402 | 1 | 100k | DNP
R14, R16, R19 | 0402 | 3 | 1k
R15, R28, R29, R30, R31 | 0402 | 5 | 100k
R18 | 0603 | 1 | 4k3
R20, R21, R22, R23 | 0402 | 4 | 1Meg
R32, R33, R34, R35, R36, R37, R38, R39, R43, R56, R57, R58, R59 | 0402 | 13 | 4k7
R44, R45, R46, R48 | 0603 | 4 | 5k9
R47, R49 | 0603 | 2 | 5k11
R50, R51, R52, R54 | 0603 | 4 | 1k33
R53, R55 | 0603 | 2 | 909R
R60, R61, R62, R63 | 0402 | 4 | 10R
R64 | 0603 | 1 | 130R
R65 | 0603 | 1 | 390R
R66 | 0402 | 1 | 470R
R67 | 0402 | 1 | 1k2
R68 | 0402 | 1 | 120R
R69 | 0603 | 1 | 196R
R70 | 4002 | 1 | 150R
R72 | 0603 | 1 | 500m
SW1 | TS-1187A-B-A-B | 1 | TS-1187A-B-A-B
SW2 | CJS-1201TB | 1 | CJS-1201TB
TP1, TP2 | TestPoint_Keystone_5019_Minature | 2 | TestPoint
U1 | ADAU1463 | 1 | ADAU1463
U10, U11, U4, U5, U6, U9 | SOIC-8_3.9x4.9mm_P1.27mm | 6 | NE5532
U12, U13 | TO-252-2 | 2 | LM317_TO-252
U2 | SOT-143_Handsoldering | 1 | ADM811
U3 | SOIC-8_3.9x4.9mm_P1.27mm | 1 | M95M01-R
U7 | TSSOP-14_4.4x5mm_P0.65mm | 1 | PCM1808
U8 | SSOP-16_3.9x4.9mm_P0.635mm | 1 | PCM1754
Y1 | Crystal_SMD_3225-4Pin_3.2x2.5mm | 1 | 830105957509

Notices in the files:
parts and their libraries:
Copyright 2016 Accelerated Designs. All rights reserved.
